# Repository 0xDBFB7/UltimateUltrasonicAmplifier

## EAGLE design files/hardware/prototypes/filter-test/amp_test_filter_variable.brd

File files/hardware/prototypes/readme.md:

I built a few laser-cut prototypes to validate the filter design. I also originally built a version using just an Attiny84, but the analog bandwidth of those series ICs is too low to be useful.

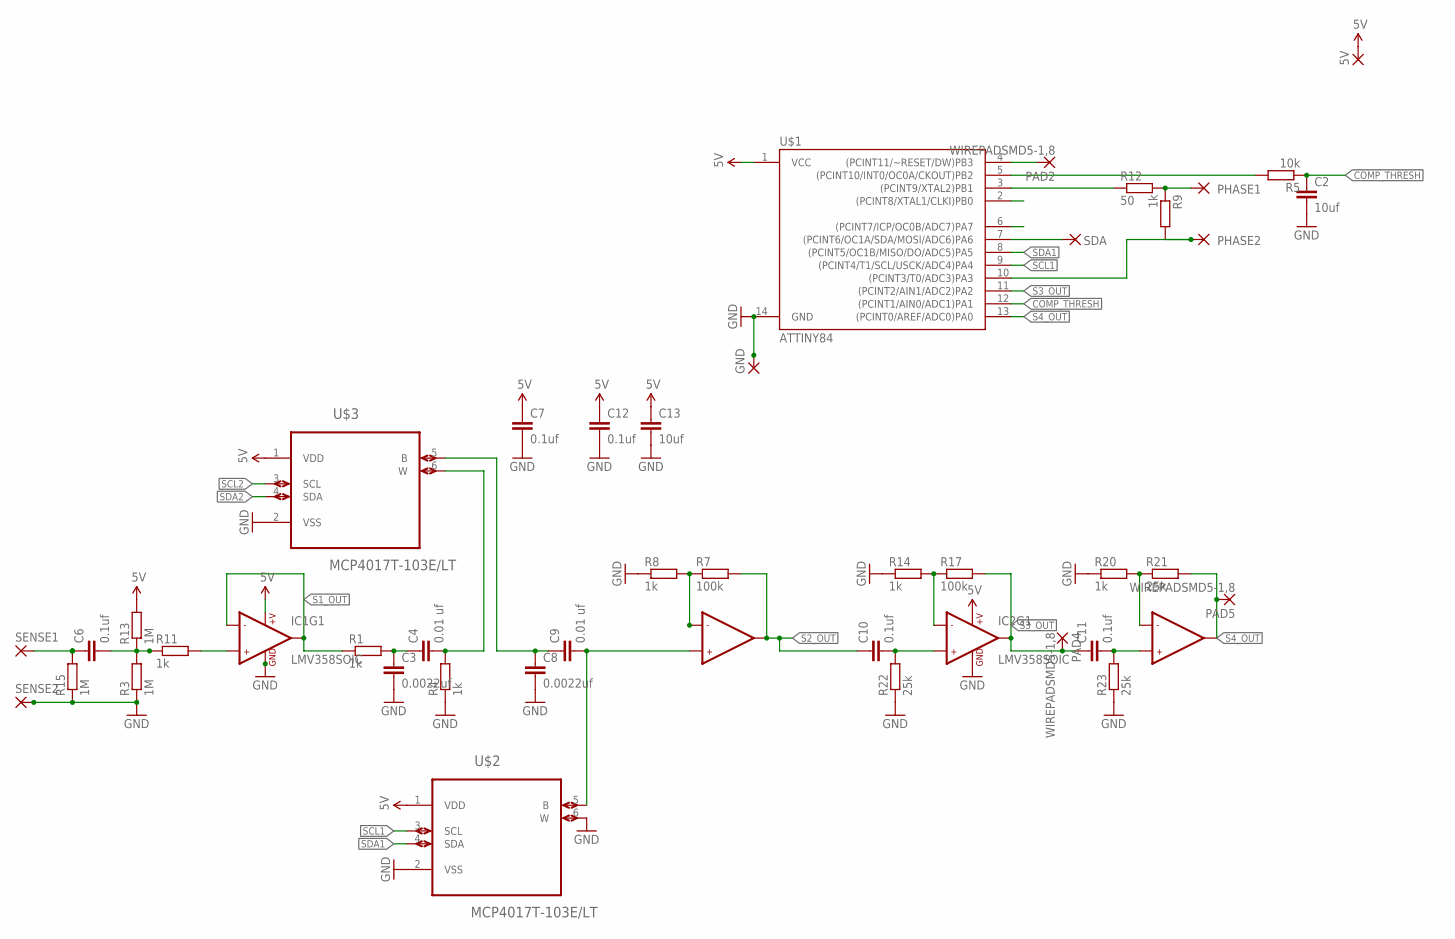
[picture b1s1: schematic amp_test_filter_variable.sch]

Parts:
5V: SMD5; SMD2,54-5,08
C2, C13: 10uf; C0603
C3, C8: 0.0022uf; C0603
C4, C9: 0.01 uf; C0603
C6, C7, C10, C11, C12: 0.1uf; C0603
GND: SMD5; SMD2,54-5,08
IC1, IC2: LMV358SOIC; SO08
PAD2, PAD4, PAD5: WIREPADSMD5-1,8; 5-1,8
PHASE1, PHASE2: SMD5; SMD2,54-5,08
R1, R4, R8, R9, R11, R14, R20: 1k; R0603
R3, R13, R15: 1M; R0603
R5: 10k; R0603
R7, R17: 100k; R0603
R12: 50; R0603
R21, R22, R23: 25k; R0603
SDA: SMD5; SMD2,54-5,08
SENSE1, SENSE2: SMD5; SMD2,54-5,08
U$1: ATTINY84; SO14
U$2, U$3: MCP4017T-103E/LT; SOT65P210X110-6N

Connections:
5V: 5V.1, C7.1, C12.1, C13.1, IC1.8 (+V), IC2.8 (+V), R13.2, U$1.1 (VCC), U$2.1 (VDD), U$3.1 (VDD)
COMP_THRESH: C2.1, R5.1, U$1.12 ((PCINT1/AIN0/ADC1)PA1)
GND: C2.2, C3.2, C7.2, C8.2, C12.2, C13.2, GND.1, IC1.4 (GND), IC2.4 (GND), R3.1, R4.1, R8.1, R14.1, R15.1, R20.1, R22.1, R23.1, SENSE2.1, U$1.14 (GND), U$2.2 (VSS), U$2.6 (W), U$3.2 (VSS)
unnamed: C10.2, IC2.3 (+IN1), R22.2
unnamed: PHASE1.1, R9.1, R12.2
unnamed: PHASE2.1, R9.2, U$1.10 ((PCINT3/T0/ADC3)PA3)
unnamed: R5.2, U$1.5 ((PCINT10/INT0/OC0A/CKOUT)PB2)
unnamed: C6.1, R15.2, SENSE1.1
unnamed: C4.2, R4.2, U$3.6 (W)
unnamed: C6.2, R3.2, R11.1, R13.1
unnamed: IC1.3 (+IN1), R11.2
unnamed: C9.2, IC1.5 (+IN2), U$2.5 (B)
unnamed: PAD2.1, U$1.4 ((PCINT11/~RESET/DW)PB3)
unnamed: C3.1, C4.1, R1.2
unnamed: R12.1, U$1.3 ((PCINT9/XTAL2)PB1)
unnamed: C11.2, IC2.5 (+IN2), R23.2
unnamed: IC1.6 (-IN2), R7.1, R8.2
unnamed: IC2.2 (-IN1), R14.2, R17.1
unnamed: C8.1, C9.1, U$3.5 (B)
unnamed: IC2.6 (-IN2), R20.2, R21.1
S1_OUT: IC1.1 (OUT1), IC1.2 (-IN1), R1.1
S2_OUT: C10.1, IC1.7 (OUT2), R7.2
S3_OUT: C11.1, IC2.1 (OUT1), PAD4.1, R17.2, U$1.11 ((PCINT2/AIN1/ADC2)PA2)
S4_OUT: IC2.7 (OUT2), PAD5.1, R21.2, U$1.13 ((PCINT0/AREF/ADC0)PA0)
SCL1: U$1.9 ((PCINT4/T1/SCL/USCK/ADC4)PA4), U$2.3 (SCL)
SCL2: U$1.2 ((PCINT8/XTAL1/CLKI)PB0), U$3.3 (SCL)
SDA: SDA.1, U$1.7 ((PCINT6/OC1A/SDA/MOSI/ADC6)PA6)
SDA1: U$1.8 ((PCINT5/OC1B/MISO/DO/ADC5)PA5), U$2.4 (SDA)
SDA2: U$1.6 ((PCINT7/ICP/OC0B/ADC7)PA7), U$3.4 (SDA)

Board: 2 copper layers, 43 parts (0 on the bottom side), 29 nets, no tracks yet.

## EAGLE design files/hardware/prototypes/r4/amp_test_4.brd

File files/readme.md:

The footprint on the first revision of the board was for a leadless package, but the STM32F030 that I originally planned to use did not have a QFN version. I therefore had to upgrade to an STM32F051 for testing before the board re-spin (putting a piece of Kapton under the exposed ground pad).

The project was abandoned before the second board re-spin, so the STM32F051 code is more developed.

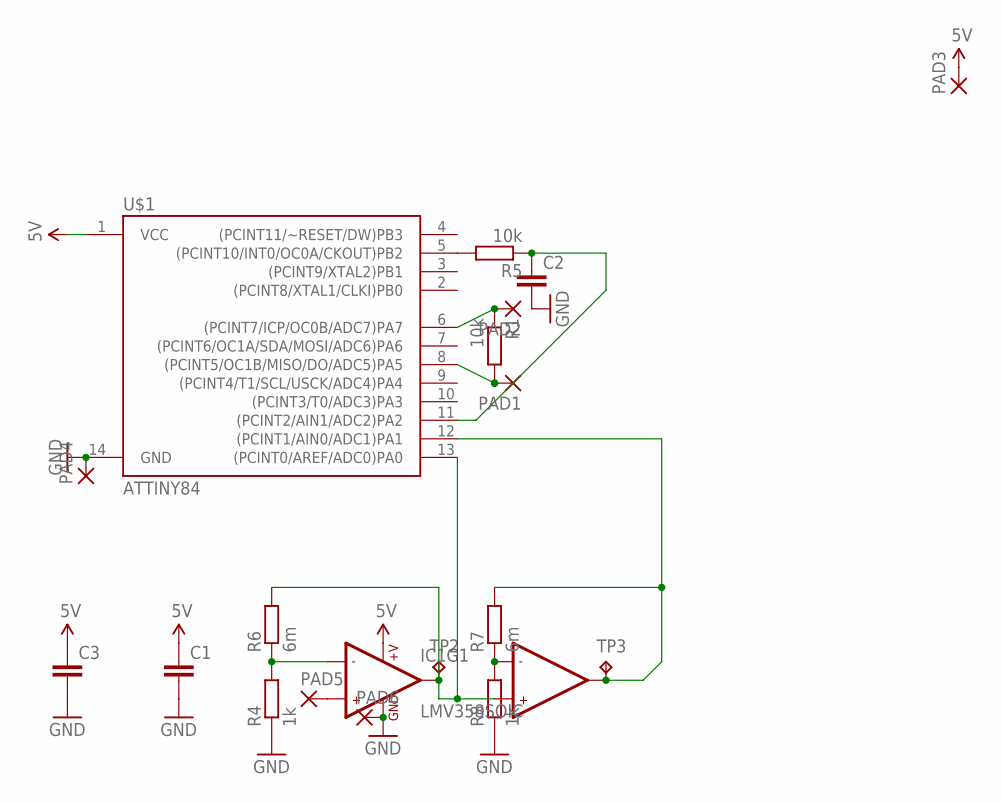
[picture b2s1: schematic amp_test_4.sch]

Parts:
C1, C2, C3: C-EUC0603; C0603
IC1: LMV358SOIC; SO08
PAD1, PAD2, PAD3, PAD4, PAD5, PAD6: SMD5; SMD2,54-5,08
R1, R5: 10k; R0603
R4, R8: 1k; R0603
R6, R7: 6m; R0603
TP2, TP3: TPTP20SQ; TP20SQ
U$1: ATTINY84; SO14

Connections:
5V: C1.1, C3.1, IC1.8 (+V), PAD3.1, U$1.1 (VCC)
GND: C1.2, C2.2, C3.2, IC1.4 (GND), PAD4.1, PAD6.1, R4.1, R8.1, U$1.14 (GND)
unnamed: PAD1.1, R1.2, U$1.8 ((PCINT5/OC1B/MISO/DO/ADC5)PA5)
unnamed: PAD2.1, R1.1, U$1.6 ((PCINT7/ICP/OC0B/ADC7)PA7)
unnamed: R5.2, U$1.5 ((PCINT10/INT0/OC0A/CKOUT)PB2)
unnamed: IC1.2 (-IN1), R4.2, R6.1
unnamed: IC1.1 (OUT1), IC1.5 (+IN2), R6.2, TP2.TP, U$1.13 ((PCINT0/AREF/ADC0)PA0)
unnamed: C2.1, R5.1, U$1.11 ((PCINT2/AIN1/ADC2)PA2)
unnamed: IC1.7 (OUT2), R7.2, TP3.TP, U$1.12 ((PCINT1/AIN0/ADC1)PA1)
unnamed: IC1.3 (+IN1), PAD5.1
unnamed: IC1.6 (-IN2), R7.1, R8.2

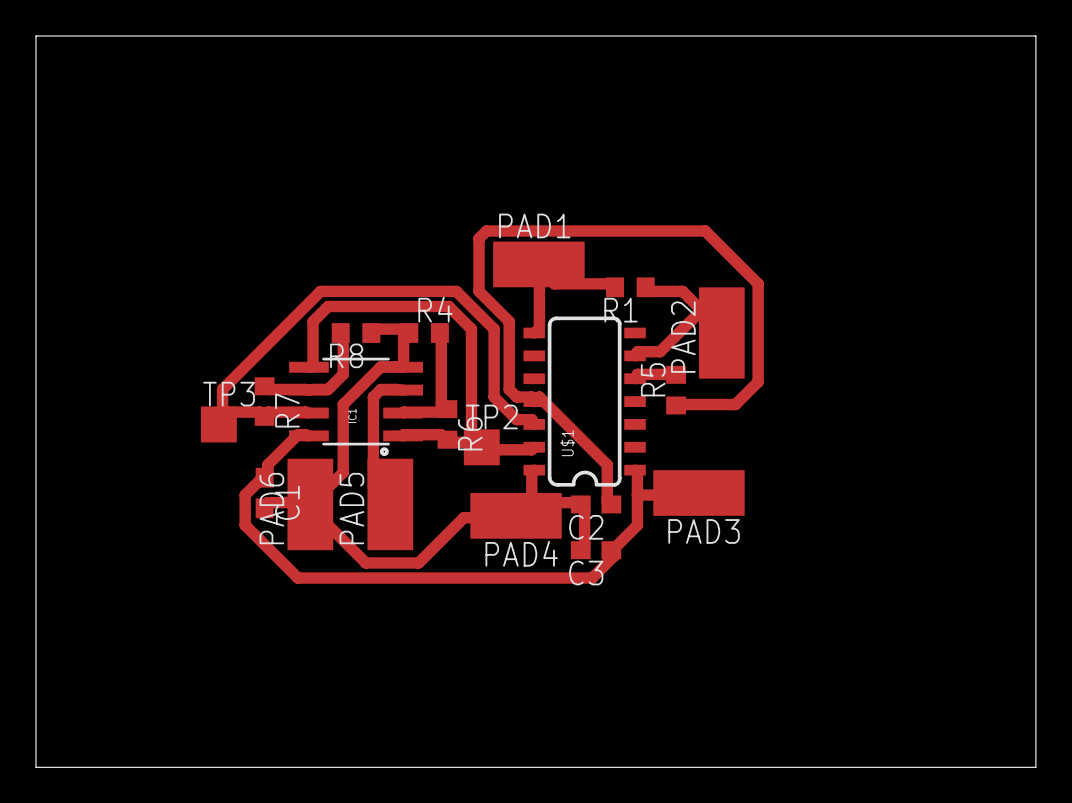
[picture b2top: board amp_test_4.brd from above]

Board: 2 copper layers, 55.5 x 40.6 mm, 19 parts (0 on the bottom side), 11 nets.

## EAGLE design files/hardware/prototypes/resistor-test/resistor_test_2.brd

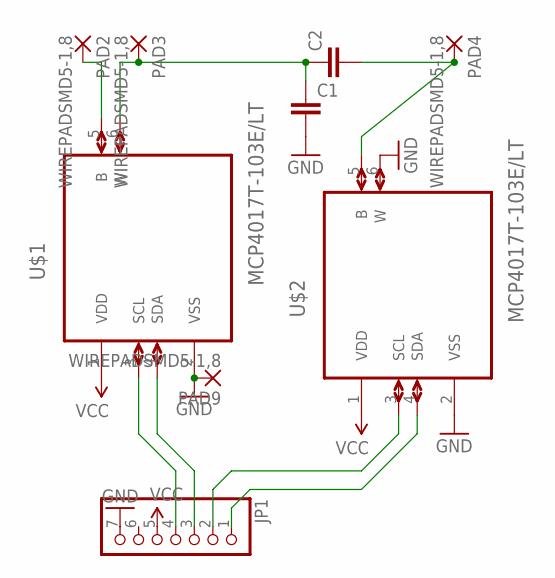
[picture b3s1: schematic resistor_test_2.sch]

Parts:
C1, C2: C-EUC0603; C0603
JP1: PINHD-1X7; 1X07
PAD2, PAD3, PAD4, PAD9: WIREPADSMD5-1,8; 5-1,8
U$1, U$2: MCP4017T-103E/LT; SOT65P210X110-6N

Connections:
GND: C1.2, JP1.7, PAD9.1, U$1.2 (VSS), U$2.2 (VSS), U$2.6 (W)
unnamed: JP1.4, U$1.3 (SCL)
unnamed: JP1.3, U$1.4 (SDA)
unnamed: JP1.2, U$2.3 (SCL)
unnamed: JP1.1, U$2.4 (SDA)
unnamed: C1.1, C2.1, PAD3.1, U$1.6 (W)
unnamed: C2.2, PAD4.1, U$2.5 (B)
unnamed: PAD2.1, U$1.5 (B)
VCC: JP1.5, U$1.1 (VDD), U$2.1 (VDD)

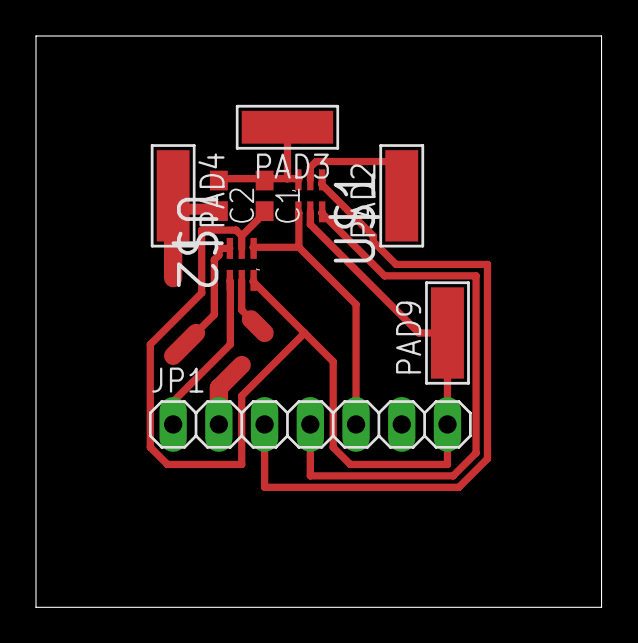
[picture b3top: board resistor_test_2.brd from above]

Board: 2 copper layers, 31.4 x 31.7 mm, 9 parts (0 on the bottom side), 9 nets.

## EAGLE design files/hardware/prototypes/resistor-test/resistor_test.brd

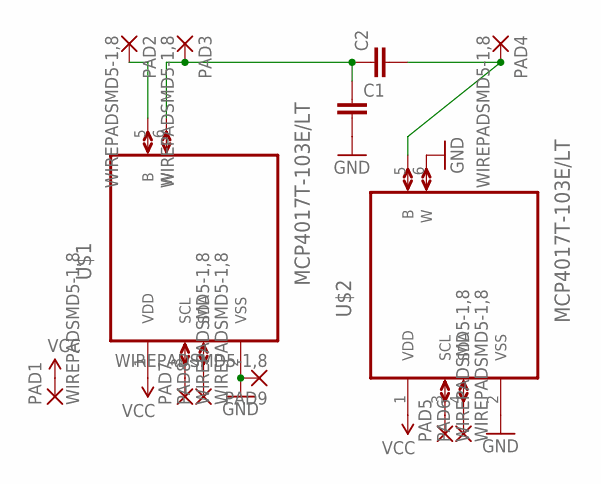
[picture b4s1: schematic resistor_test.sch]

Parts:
C1, C2: C-EUC0603; C0603
PAD1, PAD2, PAD3, PAD4, PAD5, PAD6, PAD7, PAD8, PAD9: WIREPADSMD5-1,8; 5-1,8
U$1, U$2: MCP4017T-103E/LT; SOT65P210X110-6N

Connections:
GND: C1.2, PAD9.1, U$1.2 (VSS), U$2.2 (VSS), U$2.6 (W)
unnamed: PAD5.1, U$2.3 (SCL)
unnamed: PAD6.1, U$2.4 (SDA)
unnamed: PAD7.1, U$1.3 (SCL)
unnamed: PAD8.1, U$1.4 (SDA)
unnamed: C1.1, C2.1, PAD3.1, U$1.6 (W)
unnamed: C2.2, PAD4.1, U$2.5 (B)
unnamed: PAD2.1, U$1.5 (B)
VCC: PAD1.1, U$1.1 (VDD), U$2.1 (VDD)

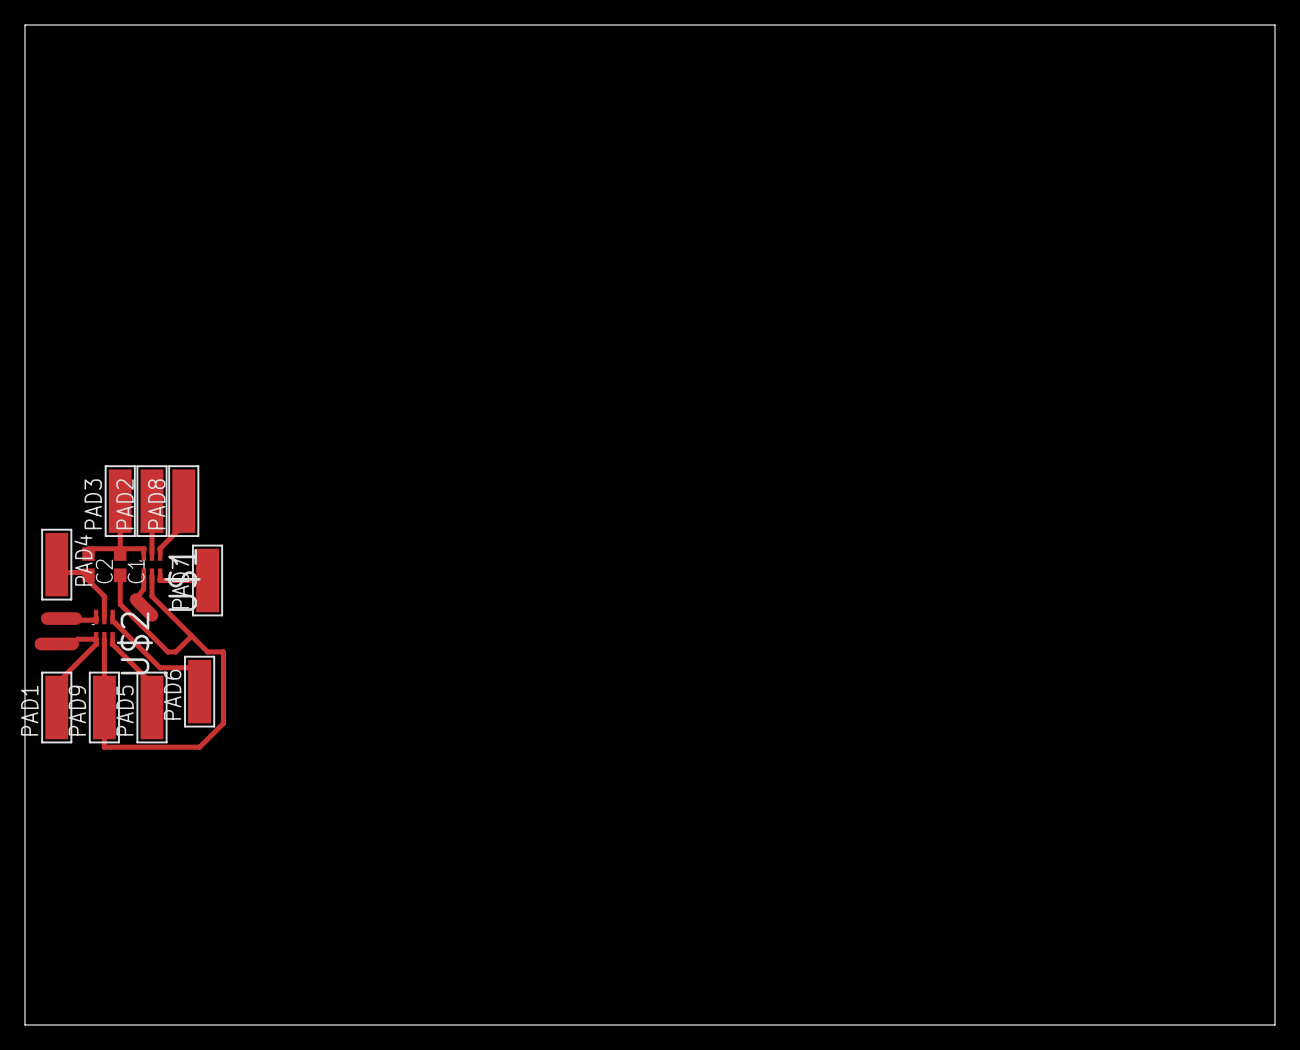
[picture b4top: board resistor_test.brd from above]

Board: 2 copper layers, 100.0 x 80.0 mm, 13 parts (0 on the bottom side), 9 nets.

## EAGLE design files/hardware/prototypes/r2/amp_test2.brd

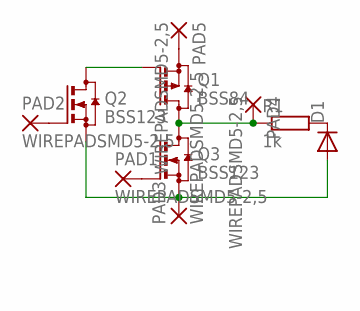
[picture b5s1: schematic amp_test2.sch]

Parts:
D1: DIODE-SOD323-R; SOD323-R
PAD1, PAD2, PAD3, PAD4, PAD5: WIREPADSMD5-2,5; 5-2,5
Q1: BSS84; SOT23
Q2, Q3: BSS123; SOT23
R1: 1k; R0603

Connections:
unnamed: PAD1.1, Q3.1 (G)
unnamed: PAD2.1, Q2.1 (G)
unnamed: D1.A, PAD3.1, Q2.2 (S), Q3.2 (S)
unnamed: PAD4.1, Q1.3 (D), Q3.3 (D), R1.1
unnamed: D1.C, R1.2
unnamed: Q1.1 (G), Q2.3 (D)
unnamed: PAD5.1, Q1.2 (S)

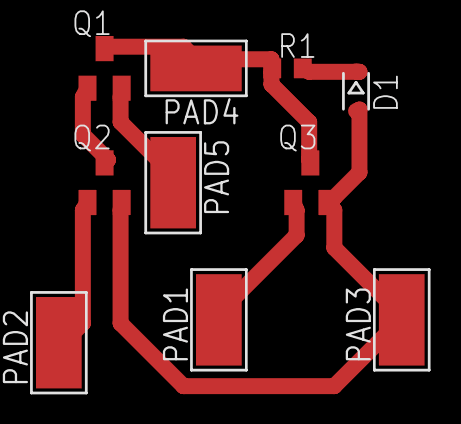
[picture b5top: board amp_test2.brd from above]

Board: 2 copper layers, 10 parts (0 on the bottom side), 7 nets.

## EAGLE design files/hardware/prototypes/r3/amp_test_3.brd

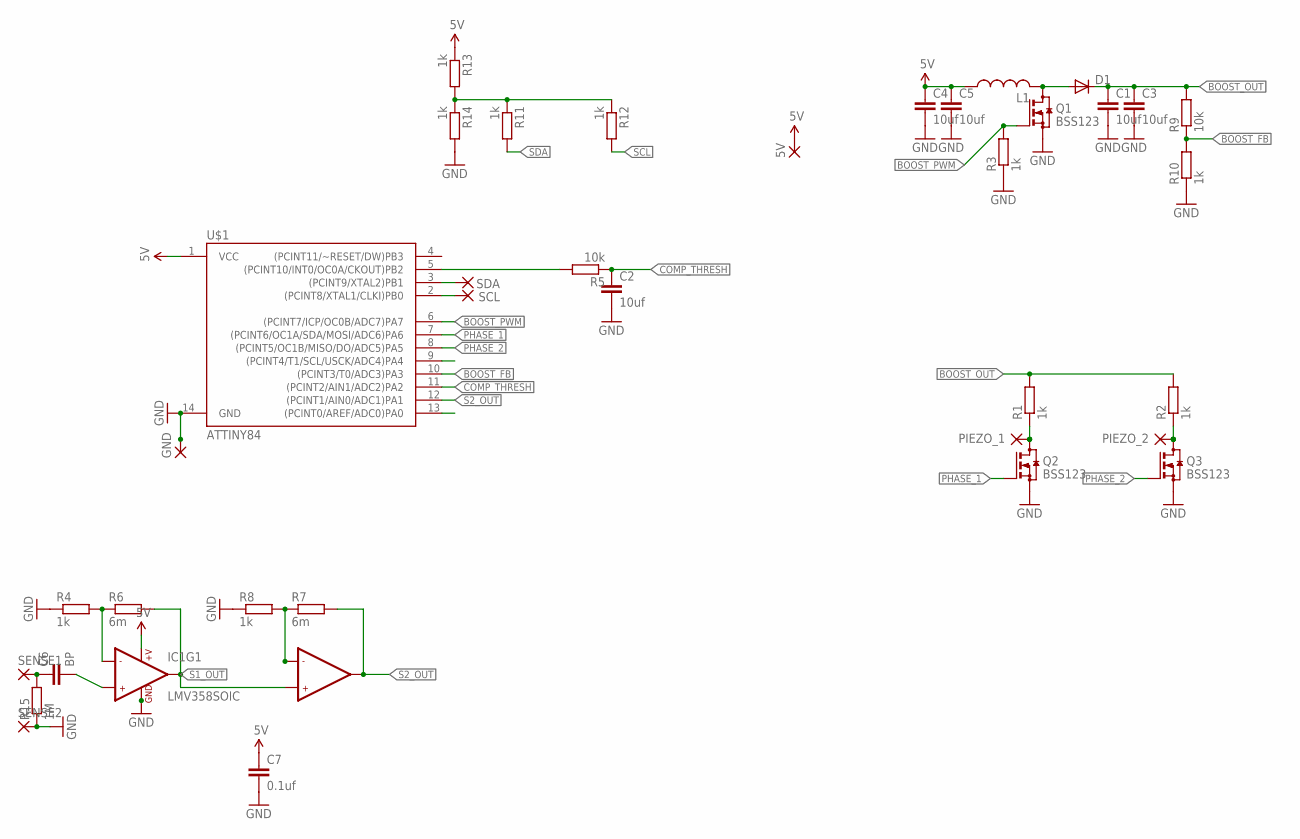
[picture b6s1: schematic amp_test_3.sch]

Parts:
5V: SMD5; SMD2,54-5,08
C1, C2, C3, C4, C5: 10uf; C0603
C6: BP; C0603
C7: 0.1uf; C0603
D1: CGRM4001-G; SOD-123_MINI-SMA
GND: SMD5; SMD2,54-5,08
IC1: LMV358SOIC; SO08
L1: L-USL2825P; L2825P
PIEZO_1, PIEZO_2: SMD5; SMD2,54-5,08
Q1, Q2, Q3: BSS123; SOT23
R1, R2, R3, R4, R8, R10, R11, R12, R13, R14: 1k; R0603
R5, R9: 10k; R0603
R6, R7: 6m; R0603
R15: 1M; R0603
SCL: SMD5; SMD2,54-5,08
SDA: SMD5; SMD2,54-5,08
SENSE1, SENSE2: SMD5; SMD2,54-5,08
U$1: ATTINY84; SO14

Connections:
5V: 5V.1, C4.1, C5.1, C7.1, IC1.8 (+V), L1.1, R13.1, U$1.1 (VCC)
BOOST_FB: R9.1, R10.2, U$1.10 ((PCINT3/T0/ADC3)PA3)
BOOST_OUT: C1.1, C3.1, D1.C, R1.2, R2.2, R9.2
BOOST_PWM: Q1.1 (G), R3.2, U$1.6 ((PCINT7/ICP/OC0B/ADC7)PA7)
COMP_THRESH: C2.1, R5.1, U$1.11 ((PCINT2/AIN1/ADC2)PA2)
GND: C1.2, C2.2, C3.2, C4.2, C5.2, C7.2, GND.1, IC1.4 (GND), Q1.2 (S), Q2.2 (S), Q3.2 (S), R3.1, R4.1, R8.1, R10.1, R14.2, R15.1, SENSE2.1, U$1.14 (GND)
unnamed: PIEZO_1.1, Q2.3 (D), R1.1
unnamed: PIEZO_2.1, Q3.3 (D), R2.1
unnamed: D1.A, L1.2, Q1.3 (D)
unnamed: R5.2, U$1.5 ((PCINT10/INT0/OC0A/CKOUT)PB2)
unnamed: C6.1, R15.2, SENSE1.1
unnamed: C6.2, IC1.3 (+IN1)
unnamed: R11.1, R12.1, R13.2, R14.1
unnamed: IC1.2 (-IN1), R4.2, R6.1
unnamed: IC1.6 (-IN2), R7.1, R8.2
PHASE_1: Q2.1 (G), U$1.7 ((PCINT6/OC1A/SDA/MOSI/ADC6)PA6)
PHASE_2: Q3.1 (G), U$1.8 ((PCINT5/OC1B/MISO/DO/ADC5)PA5)
S1_OUT: IC1.1 (OUT1), IC1.5 (+IN2), R6.2
S2_OUT: IC1.7 (OUT2), R7.2, U$1.12 ((PCINT1/AIN0/ADC1)PA1)
SCL: R12.2, SCL.1, U$1.2 ((PCINT8/XTAL1/CLKI)PB0)
SDA: R11.2, SDA.1, U$1.3 ((PCINT9/XTAL2)PB1)

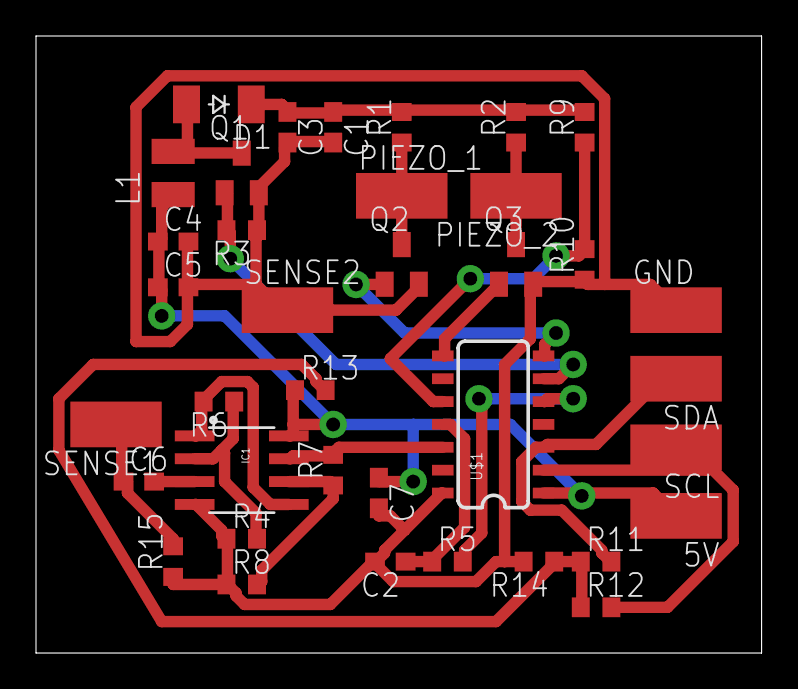
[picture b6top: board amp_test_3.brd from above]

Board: 2 copper layers, 40.3 x 34.3 mm, 37 parts (0 on the bottom side), 21 nets.

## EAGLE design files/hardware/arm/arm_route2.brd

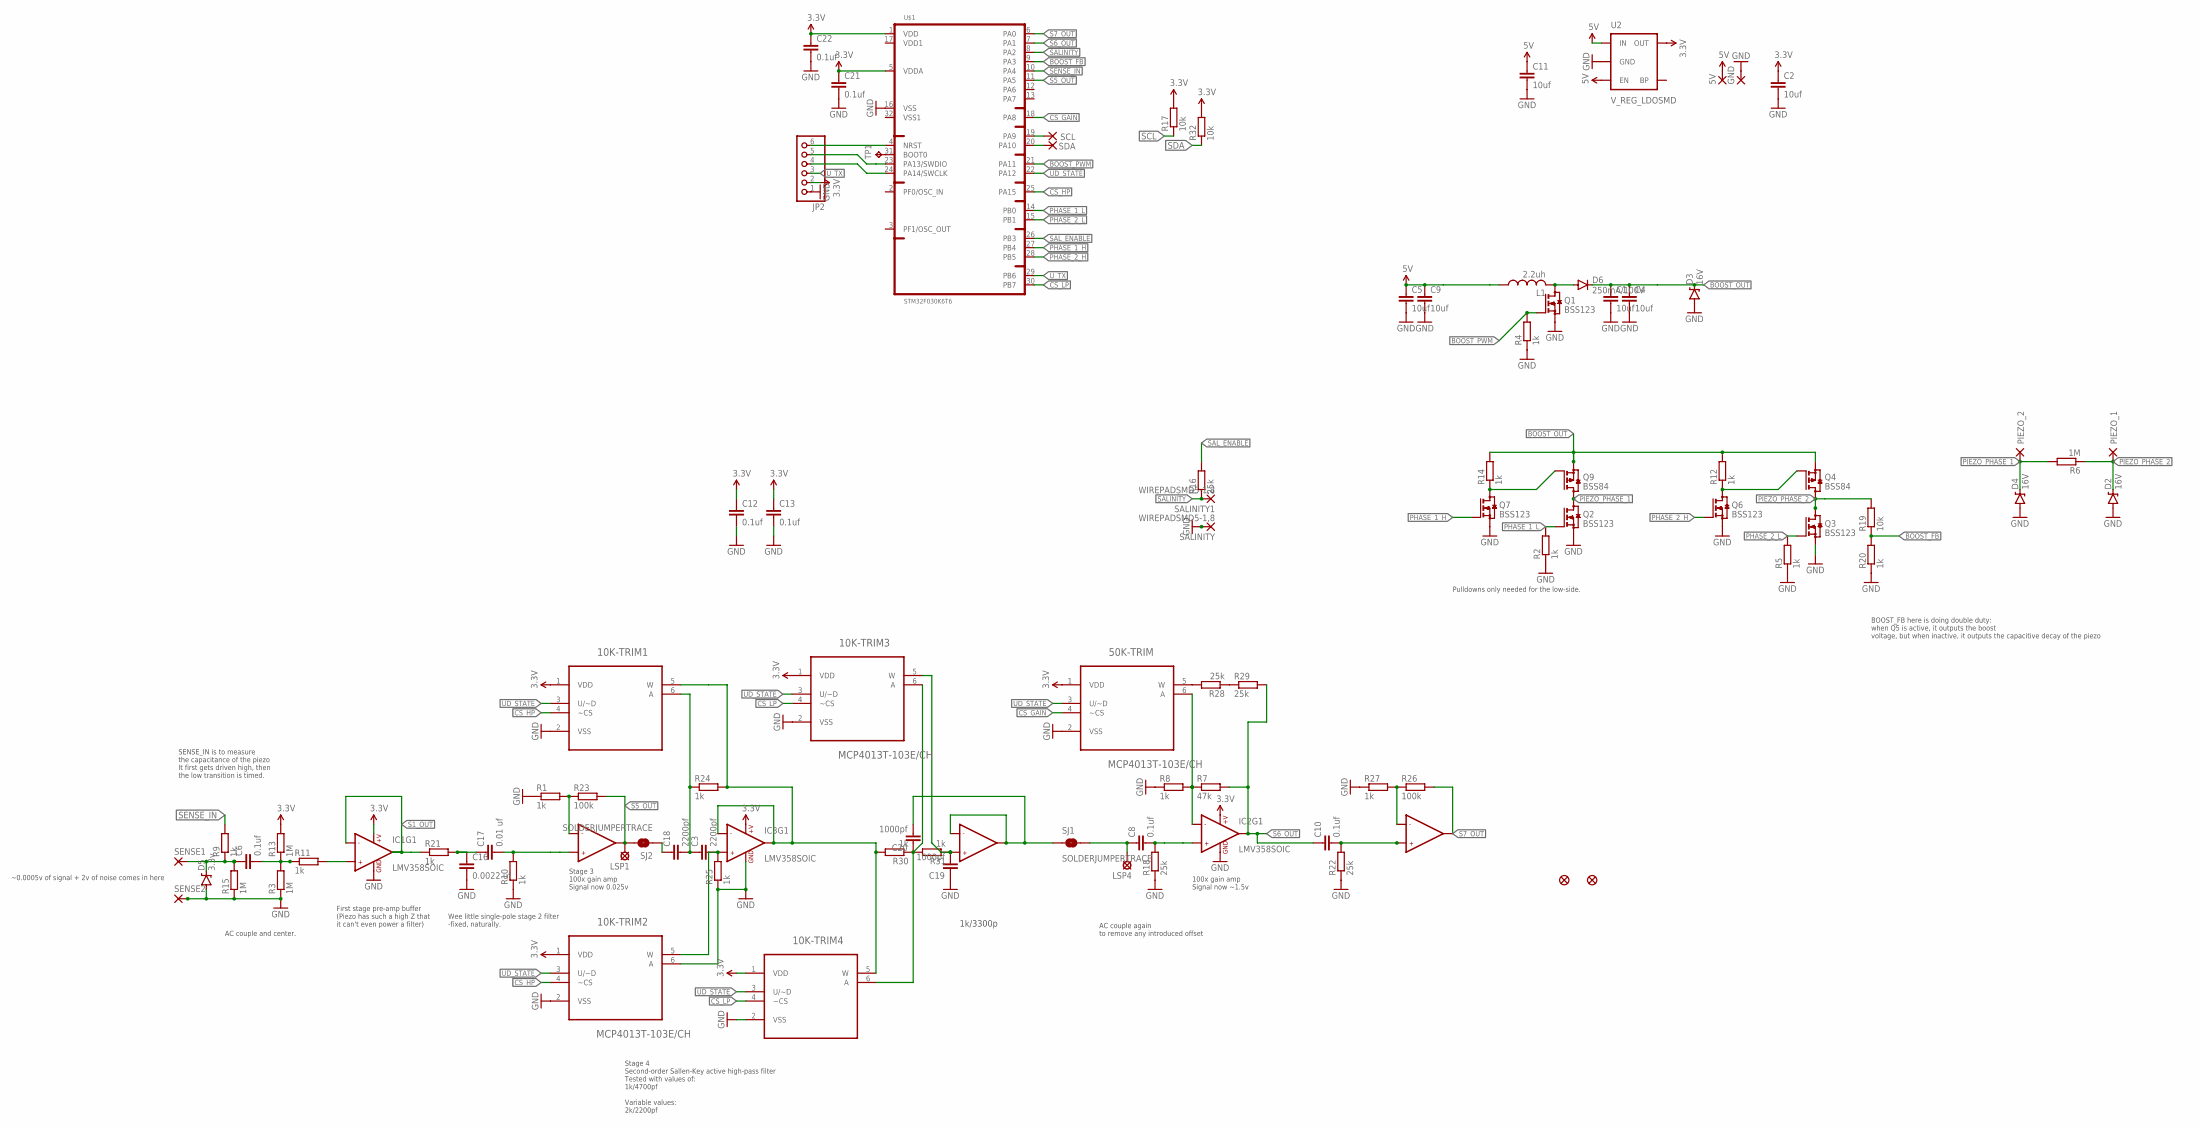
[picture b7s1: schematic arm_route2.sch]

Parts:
5V: SMD5; SMD2,54-5,08
10K-TRIM1, 10K-TRIM2, 10K-TRIM3, 10K-TRIM4, 50K-TRIM: MCP4013T-103E/CH; SOT95P280X145-6N
C1, C4: 10uf; C0805
C2, C5, C9, C11: 10uf; C0603
C3, C18: 2200pf; C0603
C6, C8, C10, C12, C13, C21, C22: 0.1uf; C0603
C16: 0.0022 uf; C0603
C17: 0.01 uf; C0603
C19, C20: 1000pf; C0603
D2, D3, D4: 16V; SOD-323
D5: 3.3v; SOD-323
D6: 250mA/100V; SOD-323
FID1, FID2: FIDUCIAL1.5X3; FIDUCIAL-1.5X3
GND: SMD5; SMD2,54-5,08
IC1, IC2, IC3: LMV358SOIC; SO08
JP2: PINHD-1X6; 1X06
L1: 2.2uh; L2825P
LSP1, LSP4: LSP10
PIEZO_1, PIEZO_2: SMD5; SMD2,54-5,08
Q1, Q2, Q3, Q6, Q7: BSS123; SOT23
Q4, Q9: BSS84; SOT23
R1, R2, R4, R5, R8, R9, R10, R11, R12, R14, R20, R21, R24, R25, R27, R30, R31: 1k; R0603
R3, R6, R13, R15: 1M; R0603
R7: 47k; R0603
R16, R18, R22, R28, R29: 25k; R0603
R17, R19, R32: 10k; R0603
R23, R26: 100k; R0603
SALINITY, SALINITY1: WIREPADSMD5-1,8; 5-1,8
SCL: SMD5; SMD2,54-5,08
SDA: SMD5; SMD2,54-5,08
SENSE1, SENSE2: SMD5; SMD2,54-5,08
SJ1, SJ2: SOLDERJUMPERTRACE; SJ_2S-TRACE
TP1: TPTP12R; TP12R
U2: V_REG_LDOSMD; SOT23-5
U$1: STM32F030K6T6; LQFP-32

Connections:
3.3V: 10K-TRIM1.1 (VDD), 10K-TRIM2.1 (VDD), 10K-TRIM3.1 (VDD), 10K-TRIM4.1 (VDD), 50K-TRIM.1 (VDD), C2.1, C12.1, C13.1, C21.1, C22.1, IC1.8 (+V), IC2.8 (+V), IC3.8 (+V), JP2.2, R13.2, R17.2, R32.2, U2.5 (OUT), U$1.1 (VDD), U$1.5 (VDDA)
5V: 5V.1, C5.1, C9.1, C11.1, L1.1, U2.1 (IN), U2.3 (EN)
BOOST_FB: R19.1, R20.2, U$1.9 (PA3)
BOOST_OUT: C1.1, C4.1, D3.C, D6.C, Q4.2 (S), Q9.2 (S), R12.2, R14.2
BOOST_PWM: Q1.1 (G), R4.2, U$1.21 (PA11)
CS_GAIN: 50K-TRIM.4 (~CS), U$1.18 (PA8)
CS_HP: 10K-TRIM1.4 (~CS), 10K-TRIM2.4 (~CS), U$1.25 (PA15)
CS_LP: 10K-TRIM3.4 (~CS), 10K-TRIM4.4 (~CS), U$1.30 (PB7)
GND: 10K-TRIM1.2 (VSS), 10K-TRIM2.2 (VSS), 10K-TRIM2.6 (A), 10K-TRIM3.2 (VSS), 10K-TRIM4.2 (VSS), 50K-TRIM.2 (VSS), C1.2, C2.2, C4.2, C5.2, C9.2, C11.2, C12.2, C13.2, C16.2, C19.1, C21.2, C22.2, D2.A, D3.A, D4.A, D5.A, GND.1, IC1.4 (GND), IC2.4 (GND), IC3.4 (GND), JP2.1, Q1.2 (S), Q2.2 (S), Q3.2 (S), Q6.2 (S), Q7.2 (S), R1.1, R2.1, R3.1, R4.1, R5.1, R8.1, R10.1, R15.1, R18.1, R20.1, R22.1, R25.1, R27.1, SALINITY.1, SENSE2.1, U2.2 (GND), U$1.16 (VSS)
unnamed: C10.2, IC2.5 (+IN2), R22.2
unnamed: Q4.1 (G), Q6.3 (D), R12.1
unnamed: C20.2, IC3.6 (-IN2), IC3.7 (OUT2), SJ1.1
unnamed: Q7.3 (D), Q9.1 (G), R14.1
unnamed: TP1.TP, U$1.31 (BOOT0)
unnamed: D6.A, L1.2, Q1.3 (D)
unnamed: C6.2, R3.2, R11.1, R13.1
unnamed: IC1.3 (+IN1), R11.2
unnamed: C16.1, C17.1, R21.2
unnamed: C8.1, LSP4.MP, SJ1.2
unnamed: IC1.6 (-IN2), R1.2, R23.1
unnamed: C18.1, SJ2.1
unnamed: C17.2, IC1.5 (+IN2), R10.2
unnamed: 50K-TRIM.6 (A), IC2.2 (-IN1), R7.1, R8.2
unnamed: C8.2, IC2.3 (+IN1), R18.2
unnamed: 10K-TRIM3.5 (W), C19.2, IC3.5 (+IN2), R31.1
unnamed: 10K-TRIM2.5 (W), C3.2, IC3.3 (+IN1), R25.2
unnamed: 10K-TRIM1.5 (W), 10K-TRIM4.5 (W), IC3.1 (OUT1), IC3.2 (-IN1), R24.2, R30.2
unnamed: 10K-TRIM1.6 (A), C3.1, C18.2, R24.1
unnamed: IC2.6 (-IN2), R26.1, R27.2
unnamed: 50K-TRIM.5 (W), R28.2
unnamed: R28.1, R29.1
unnamed: 10K-TRIM3.6 (A), 10K-TRIM4.6 (A), C20.1, R30.1, R31.2
unnamed: JP2.6, U$1.4 (NRST)
unnamed: JP2.5, U$1.23 (PA13/SWDIO)
unnamed: JP2.4, U$1.24 (PA14/SWCLK)
PHASE_1_H: Q7.1 (G), U$1.27 (PB4)
PHASE_1_L: Q2.1 (G), R2.2, U$1.14 (PB0)
PHASE_2_H: Q6.1 (G), U$1.28 (PB5)
PHASE_2_L: Q3.1 (G), R5.2, U$1.15 (PB1)
PIEZO_IN: C6.1, D5.C, R9.1, R15.2, SENSE1.1
PIEZO_PHASE_1: D4.C, PIEZO_2.1, Q2.3 (D), Q9.3 (D), R6.2
PIEZO_PHASE_2: D2.C, PIEZO_1.1, Q3.3 (D), Q4.3 (D), R6.1, R19.2
S1_OUT: IC1.1 (OUT1), IC1.2 (-IN1), R21.1
S5_OUT: IC1.7 (OUT2), LSP1.MP, R23.2, SJ2.2, U$1.11 (PA5)
S6_OUT: C10.1, IC2.1 (OUT1), R7.2, R29.2, U$1.7 (PA1)
S7_OUT: IC2.7 (OUT2), R26.2, U$1.6 (PA0)
SALINITY: R16.1, SALINITY1.1, U$1.8 (PA2)
SAL_ENABLE: R16.2, U$1.26 (PB3)
SCL: R17.1, SCL.1, U$1.19 (PA9)
SDA: R32.1, SDA.1, U$1.20 (PA10)
SENSE_IN: R9.2, U$1.10 (PA4)
UD_STATE: 10K-TRIM1.3 (U/~D), 10K-TRIM2.3 (U/~D), 10K-TRIM3.3 (U/~D), 10K-TRIM4.3 (U/~D), 50K-TRIM.3 (U/~D), U$1.22 (PA12)
U_TX: JP2.3, U$1.29 (PB6)

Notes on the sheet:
BOOST_FB here is doing double duty: when Q5 is active, it outputs the boost voltage, but when inactive, it outputs the capacitive decay of the piezo
Pulldowns only needed for the low-side.
~0.0005v of signal + 2v of noise comes in here
First stage pre-amp buffer (Piezo has such a high Z that it can't even power a filter)
AC couple and center.
SENSE_IN is to measure the capacitance of the piezo It first gets driven high, then the low transition is timed.
Wee little single-pole stage 2 filter -fixed, naturally.
Stage 3 100x gain amp Signal now 0.025v
AC couple again to remove any introduced offset
Stage 4 Second-order Sallen-Key active high-pass filter Tested with values of: 1k/4700pf Variable values: 2k/2200pf
100x gain amp Signal now ~1.5v
1k/3300p

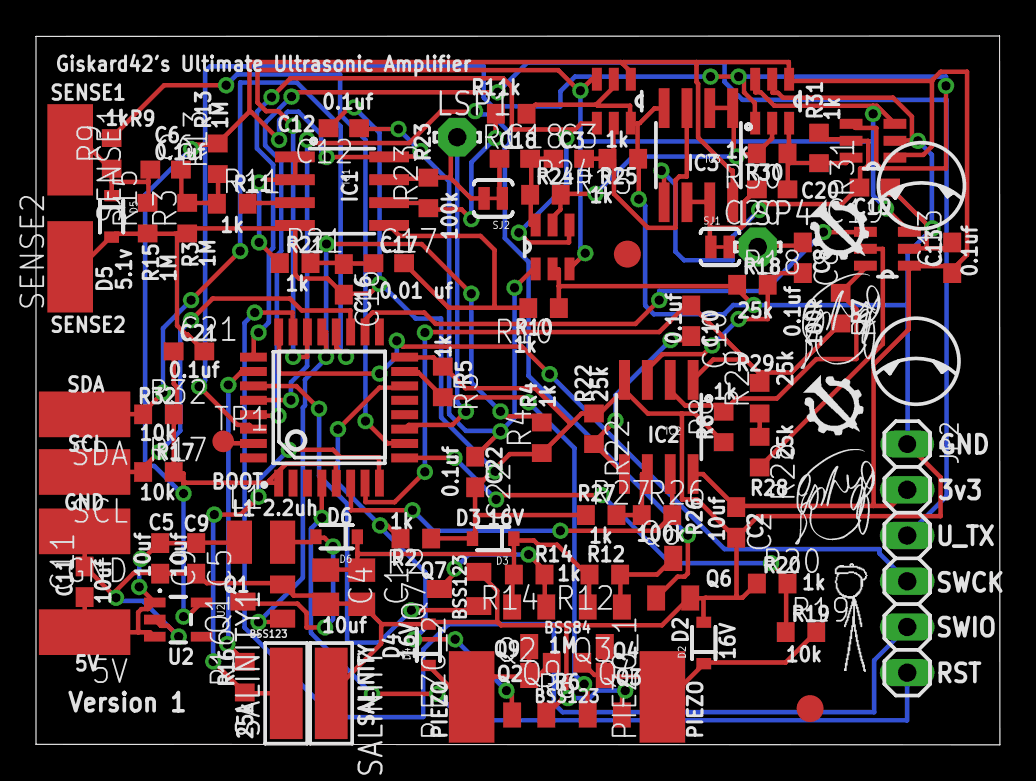
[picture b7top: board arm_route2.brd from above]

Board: 2 copper layers, 53.6 x 39.4 mm, 92 parts (0 on the bottom side), 53 nets.

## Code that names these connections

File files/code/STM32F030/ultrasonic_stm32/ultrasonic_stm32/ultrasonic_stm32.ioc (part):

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Mcu.Name=STM32F030K6Tx
Mcu.Package=LQFP32
Mcu.UserName=STM32F030K6Tx
PA0.Mode=IN0
PA0.Signal=ADC_IN0
PA1.Mode=IN1
PA1.Signal=ADC_IN1
PA10.Mode=I2C
PA10.Signal=I2C1_SDA
PA11.Signal=S_TIM1_CH4
PA12.GPIOParameters=GPIO_Label
PA12.GPIO_Label=UD_STATE
PA12.Signal=GPIO_Output
PA13.Mode=Serial_Wire
PA13.Signal=SYS_SWDIO
PA14.Mode=Serial_Wire
PA14.Signal=SYS_SWCLK
PA15.GPIOParameters=GPIO_Label
PA15.GPIO_Label=CS_HP
PA15.Signal=GPIO_Output
PA2.Mode=IN2
PA2.Signal=ADC_IN2
PA3.Mode=IN3
PA3.Signal=ADC_IN3
PA4.Mode=IN4
PA4.Signal=ADC_IN4
PA5.Mode=IN5
PA5.Signal=ADC_IN5
PA6.Signal=S_TIM16_CH1
PA7.Signal=S_TIM14_CH1
PA8.Signal=GPIO_Output
PA9.Mode=I2C
PA9.Signal=I2C1_SCL
PB0.GPIOParameters=GPIO_Label
PB0.GPIO_Label=PHASE_1_L
PB0.Signal=GPIO_Output
PB1.GPIOParameters=GPIO_Label
PB1.GPIO_Label=PHASE_2_L
PB1.Signal=GPIO_Output
PB3.GPIOParameters=GPIO_Label
PB3.GPIO_Label=CAL_ENABLE
PB3.Signal=GPIO_Output
PB4.GPIOParameters=GPIO_Label
PB4.GPIO_Label=PHASE_1_H
PB4.Signal=GPIO_Output
PB5.GPIOParameters=GPIO_Label
PB5.GPIO_Label=PHASE_2_H
PB5.Signal=GPIO_Output
PB6.Mode=Half_duplex(single_wire_mode)
PB6.Signal=USART1_TX
PB7.Signal=GPIO_Output
RCC.SYSCLKFreq_VALUE=48000000
RCC.SYSCLKSource=RCC_SYSCLKSOURCE_PLLCLK
board=ultrasonic_stm32

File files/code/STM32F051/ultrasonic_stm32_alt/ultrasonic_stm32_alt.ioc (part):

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Mcu.Name=STM32F051K6Ux
Mcu.Package=UFQFPN32
Mcu.UserName=STM32F051K6Ux
PA0.GPIOParameters=GPIO_Label
PA0.GPIO_Label=COMPARATOR
PA0.Signal=GPIO_Input
PA11.GPIOParameters=GPIO_Label
PA11.GPIO_Label=BOOST_PWM
PA11.Signal=S_TIM1_CH4
PA12.GPIOParameters=GPIO_Label
PA12.GPIO_Label=UD_STATE
PA12.Signal=GPIO_Output
PA13.Mode=Serial_Wire
PA13.Signal=SYS_SWDIO
PA14.Mode=Serial_Wire
PA14.Signal=SYS_SWCLK
PA15.GPIOParameters=GPIO_Label
PA15.GPIO_Label=CS_HP
PA15.Signal=GPIO_Output
PA3.GPIOParameters=GPIO_Label
PA3.GPIO_Label=BOOST_FB
PA3.Mode=IN3
PA3.Signal=ADC_IN3
PA4.Signal=GPIO_Input
PA8.GPIOParameters=GPIO_Label
PA8.GPIO_Label=CS_GAIN
PA8.Signal=GPIO_Output
PB0.GPIOParameters=GPIO_Label
PB0.GPIO_Label=PHASE_1_L
PB0.Signal=GPIO_Output
PB1.GPIOParameters=GPIO_Label
PB1.GPIO_Label=PHASE_2_L
PB1.Signal=GPIO_Output
PB3.GPIOParameters=GPIO_Label
PB3.GPIO_Label=SAL_ENABLE
PB3.Signal=GPIO_Output
PB4.GPIOParameters=GPIO_Label
PB4.GPIO_Label=PHASE_1_H
PB4.Signal=GPIO_Output
PB5.GPIOParameters=GPIO_Label
PB5.GPIO_Label=PHASE_2_H
PB5.Signal=GPIO_Output
PB6.Mode=Half_duplex(single_wire_mode)
PB6.Signal=USART1_TX
PB7.GPIOParameters=GPIO_Label
PB7.GPIO_Label=CS_LP
PB7.Signal=GPIO_Output
RCC.SYSCLKFreq_VALUE=48000000
RCC.SYSCLKSource=RCC_SYSCLKSOURCE_PLLCLK
board=ultrasonic_stm32_alt

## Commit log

2018-04-29 Added board files

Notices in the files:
parts and their libraries:
SparkFun-DiscreteSemi: Licensing: Creative Commons ShareAlike 4.0 International - https://creativecommons.org/licenses/by-sa/4.0
